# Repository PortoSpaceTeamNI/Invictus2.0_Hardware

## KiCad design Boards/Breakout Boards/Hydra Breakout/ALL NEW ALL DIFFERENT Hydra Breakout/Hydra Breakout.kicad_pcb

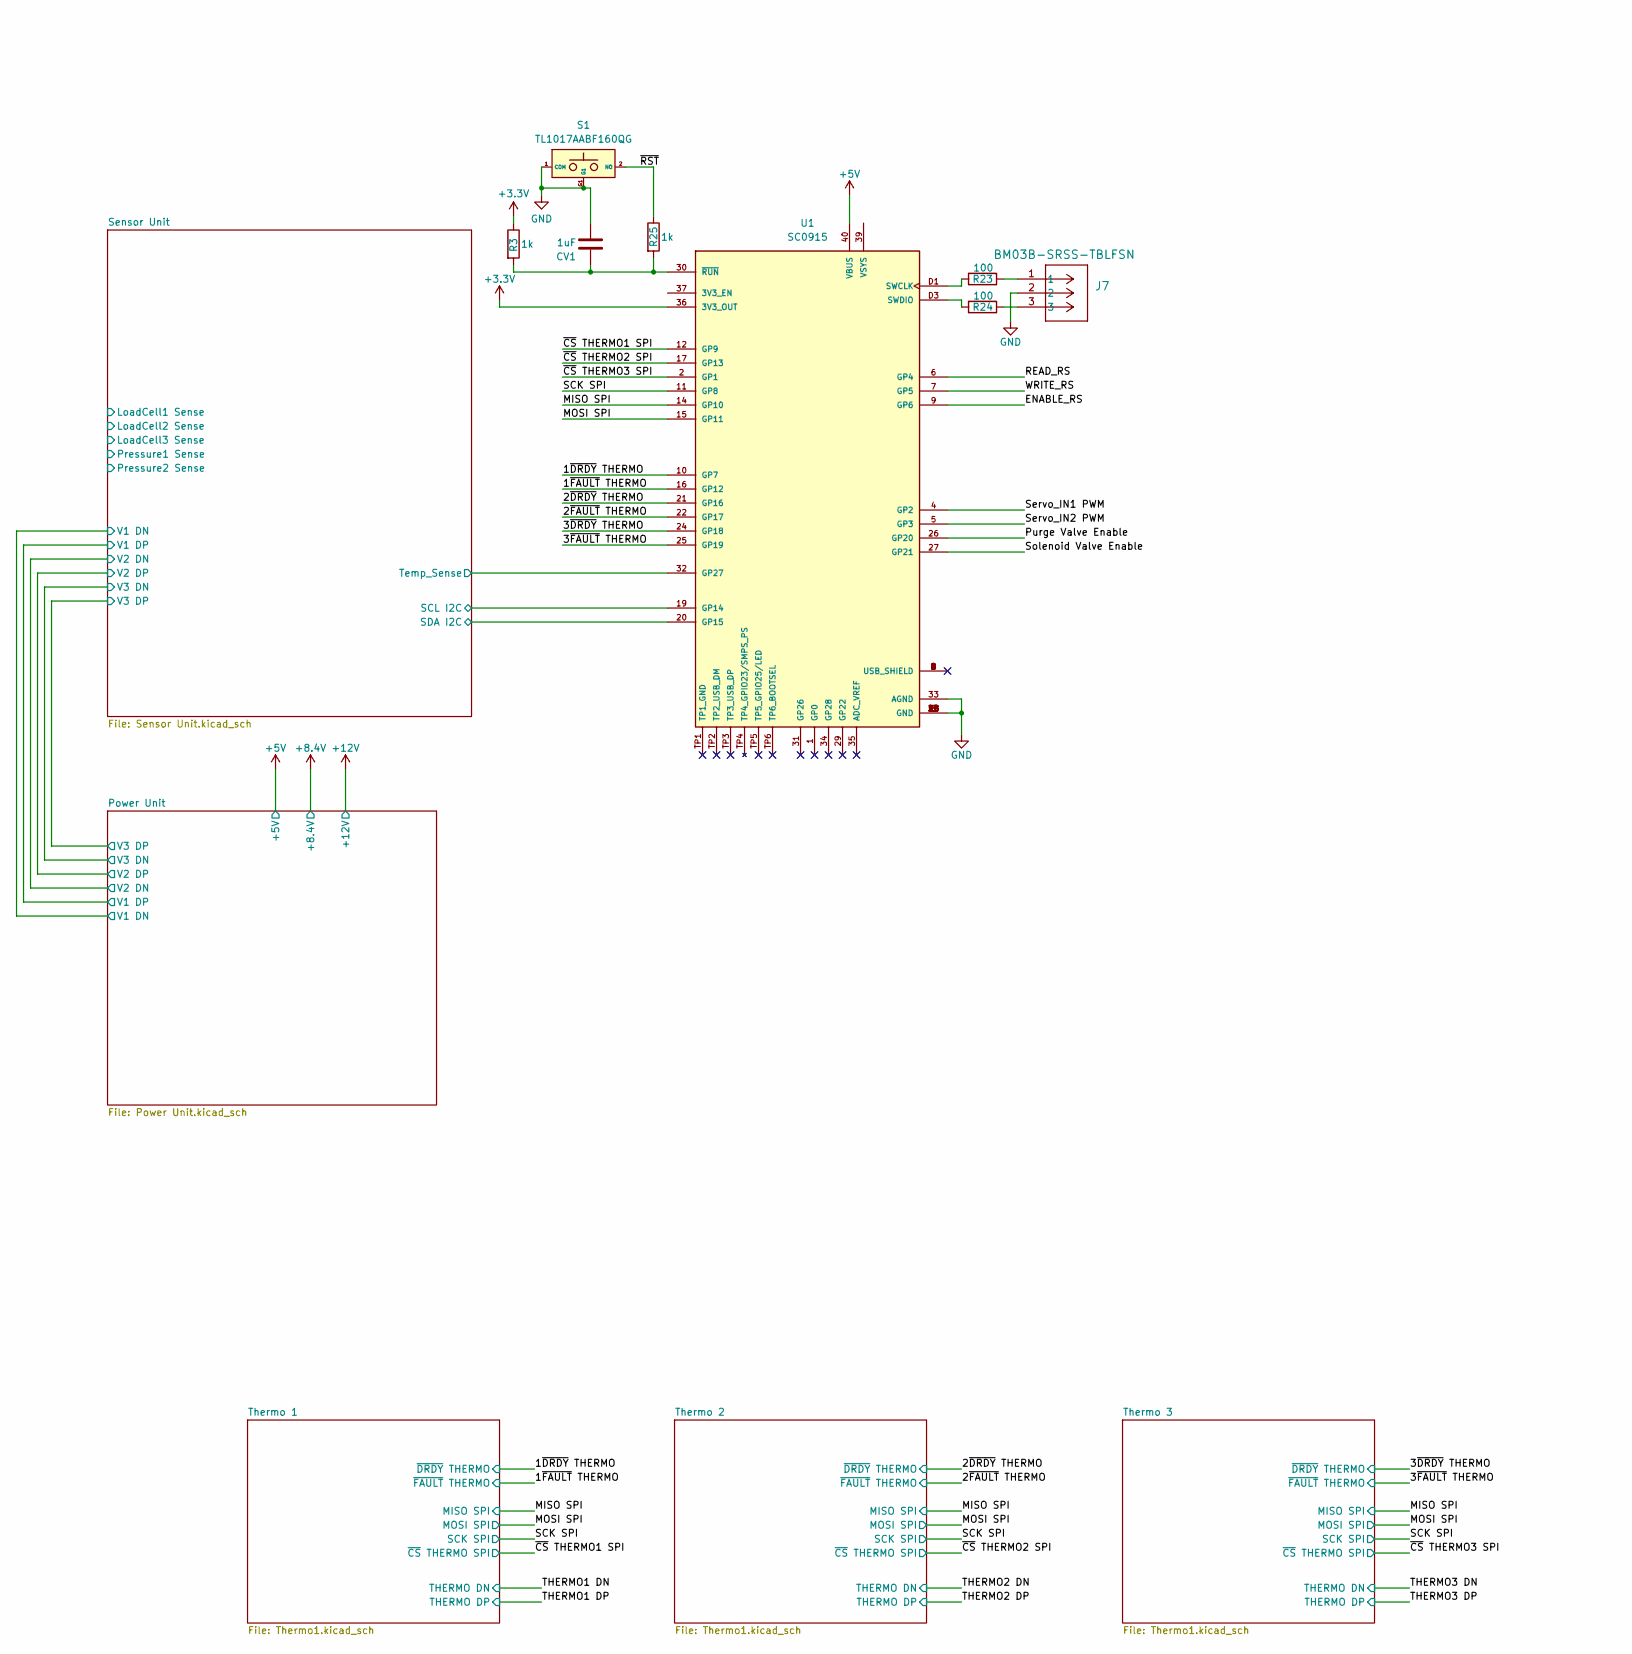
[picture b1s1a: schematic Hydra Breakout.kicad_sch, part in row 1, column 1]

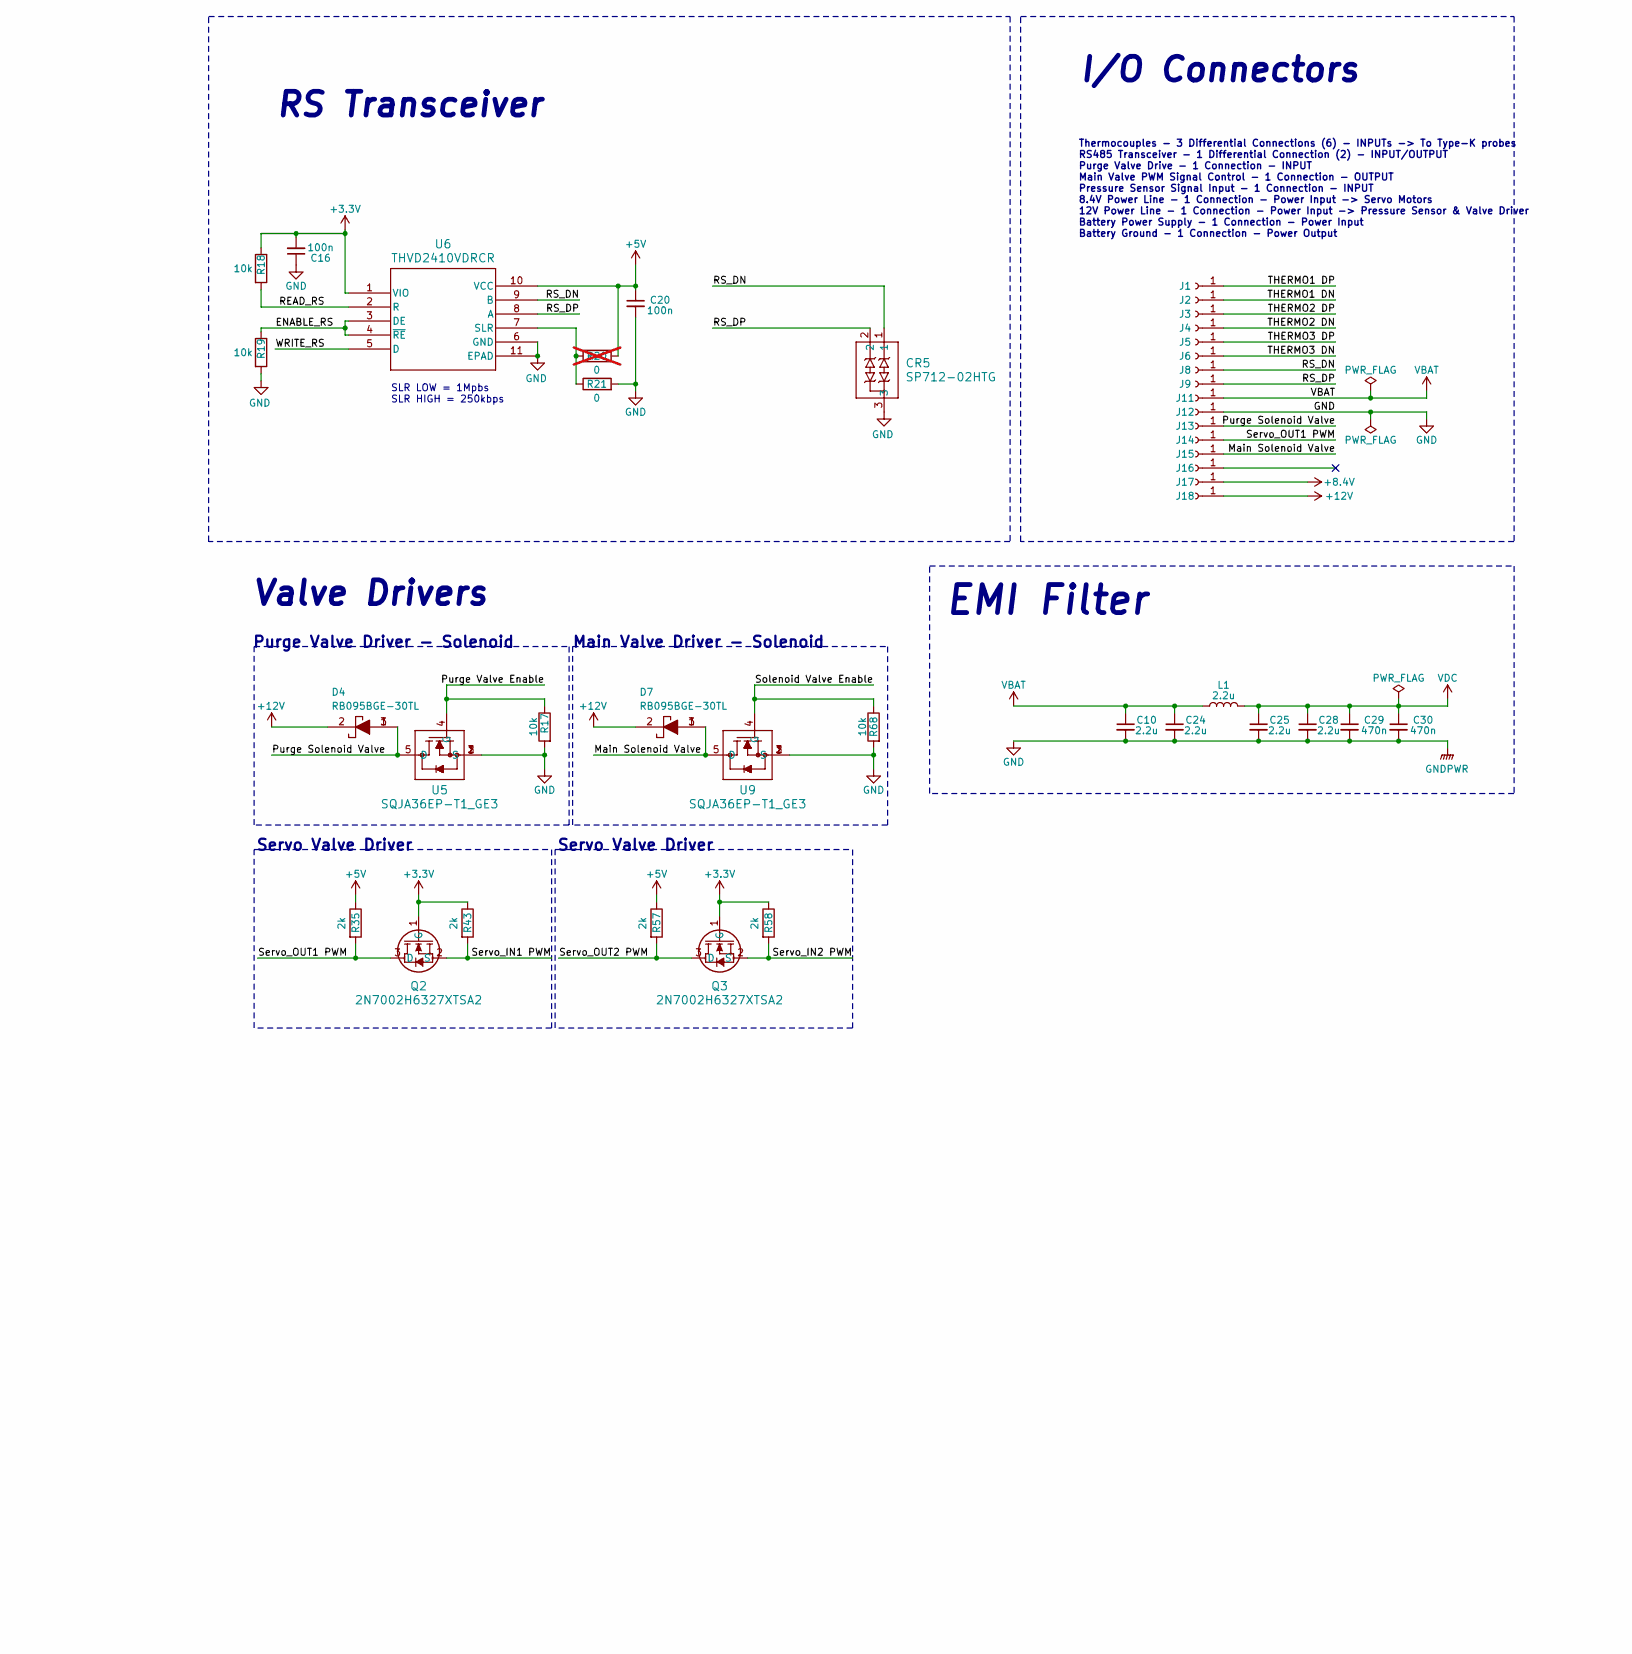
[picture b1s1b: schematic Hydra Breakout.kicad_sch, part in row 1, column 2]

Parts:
C10, C24, C25, C28: 2.2u; Capacitor_1206
C16, C20: 100n; Capacitor_0603
C29, C30: 470n; Capacitor_1206
CR5: SP712-02HTG; SOT23-3_LTF
CV1: 1uF; Capacitor_0603
D4, D7: RB095BGE-30TL; RD3P175SNFRATL; Mouser Part Number 755-RB095BGE-30TL
J1, J2, J3, J4, J5, J6, J8, J9, J11, J12, J13, J14, J15, J16, J17, J18: Conn_01x01_Socket; Pico_01pin
J7: BM03B-SRSS-TBLFSN; CONN_BM03B-SRSS-TBLFSN_JST
L1: 2.2u; IND_SPM10065VT-2R2M-D
Q2, Q3: 2N7002H6327XTSA2; PG-SOT23-3-5_INF_MIN
R3, R25: 1k; Capacitor_0603
R17, R18, R19, R68: 10k; Capacitor_0603
R20: 0; RES_0603; not fitted
R21: 0; RES_0603
R23, R24: 100; Capacitor_0603
R35, R43, R57, R58: 2k; Capacitor_0603
S1: TL1017AABF160QG; Mouser Part Number 612-TL1017AABF160QG
U1: SC0915; MODULE_SC0915; PARTREV 1.9
U5, U9: SQJA36EP-T1_GE3; PowerPAK_SO-8L_3_VIS
U6: THVD2410VDRCR; VSON10_DRC_TEX

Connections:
+3.3V: C16.2, Q2.1 (G), Q3.1 (G), R3.1, R18.1, R43.1, R58.1, U1.36 (3V3_OUT), U6.1 (VIO); also elsewhere on the board
+5V: C20.1, R20.2, R35.1, R57.1, U1.40 (VBUS), U6.10 (VCC); also elsewhere on the board
+8.4V: J17.1; also elsewhere on the board
+12V: D4.2, D7.2, J18.1; also elsewhere on the board
/1~DRDY THERMO: U1.10 (GP7); also elsewhere on the board
/1~FAULT THERMO: U1.16 (GP12); also elsewhere on the board
/2~DRDY THERMO: U1.21 (GP16); also elsewhere on the board
/2~FAULT THERMO: U1.22 (GP17); also elsewhere on the board
/3~DRDY THERMO: U1.24 (GP18); also elsewhere on the board
/3~FAULT THERMO: U1.25 (GP19); also elsewhere on the board
/ENABLE_RS: R19.1, U1.9 (GP6), U6.3 (DE), U6.4 (~RE)
/MISO SPI: U1.14 (GP10); also elsewhere on the board
/MOSI SPI: U1.15 (GP11); also elsewhere on the board
/Main Solenoid Valve: D7.1, D7.3, J15.1, U9.5 (D)
/Purge Solenoid Valve: D4.1, D4.3, J13.1, U5.5 (D)
/Purge Valve Enable: R17.1, U1.26 (GP20), U5.4 (G)
/READ_RS: R18.2, U1.6 (GP4), U6.2 (R); also elsewhere on the board
/RS_DN: CR5.1, J8.1, U6.9 (B); also elsewhere on the board
/RS_DP: CR5.2, J9.1, U6.8 (A); also elsewhere on the board
/SCK SPI: U1.11 (GP8); also elsewhere on the board
/Sensor Unit/SCL I2C: U1.19 (GP14); also elsewhere on the board
/Sensor Unit/SDA I2C: U1.20 (GP15); also elsewhere on the board
/Sensor Unit/Temp_Sense: U1.32 (GP27); also elsewhere on the board
/Servo_IN1 PWM: Q2.2 (S), R43.2, U1.4 (GP2)
/Servo_IN2 PWM: Q3.2 (S), R58.2, U1.5 (GP3)
/Servo_OUT1 PWM: J14.1, Q2.3 (D), R35.2
/Servo_OUT2 PWM: Q3.3 (D), R57.2
/Solenoid Valve Enable: R68.1, U1.27 (GP21), U9.4 (G)
/THERMO1 DN: J2.1; also elsewhere on the board
/THERMO1 DP: J1.1; also elsewhere on the board
/THERMO2 DN: J4.1; also elsewhere on the board
/THERMO2 DP: J3.1; also elsewhere on the board
/THERMO3 DN: J6.1; also elsewhere on the board
/THERMO3 DP: J5.1; also elsewhere on the board
/WRITE_RS: U1.7 (GP5), U6.5 (D)
/~CS THERMO1 SPI: U1.12 (GP9); also elsewhere on the board
/~CS THERMO2 SPI: U1.17 (GP13); also elsewhere on the board
/~CS THERMO3 SPI: U1.2 (GP1); also elsewhere on the board
/~RST: R25.1, S1.2 (NO)
GND: C10.2, C16.1, C20.2, C24.2, C25.2, C28.2, C29.2, C30.2, CR5.3, CV1.2, J7.2, J12.1, R17.2, R19.2, R21.2, R68.2, S1.1 (COM), S1.G1, U1.3 (GND), U1.8 (GND), U1.13 (GND), U1.18 (GND), U1.23 (GND), U1.28 (GND), U1.33 (AGND), U1.38 (GND), U1.D2 (GND), U5.1 (S), U5.2 (S), U5.3 (S), U6.6 (GND), U6.11 (EPAD), U9.1 (S), U9.2 (S), U9.3 (S); also elsewhere on the board
unnamed: J7.1, R23.1
unnamed: J7.3, R24.1
unnamed: R23.2, U1.D1 (SWCLK)
unnamed: R24.2, U1.D3 (SWDIO)
unnamed: CV1.1, R3.2, R25.2, U1.30 (~RUN)
unnamed: R20.1, R21.1, U6.7 (SLR)
VBAT: C10.1, C24.1, J11.1, L1.1
VDC: C25.1, C28.1, C29.1, C30.1, L1.2; also elsewhere on the board

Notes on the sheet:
EMI Filter
Thermocouples - 3 Differential Connections (6) - INPUTs -> To Type-K probes RS485 Transceiver - 1 Differential Connection (2) - INPUT/OUTPUT Purge Valve Drive - 1 Connection - INPUT Main Valve PWM Signal Control - 1 Connection - OUTPUT Pressure Sensor Signal Input - 1 Connection - INPUT 8.4V Power 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
Purge Valve Driver - Solenoid
Servo Valve Driver
SLR LOW = 1Mpbs SLR HIGH = 250kbps
I/O Connectors
Main Valve Driver - Solenoid
RS Transceiver
Valve Drivers

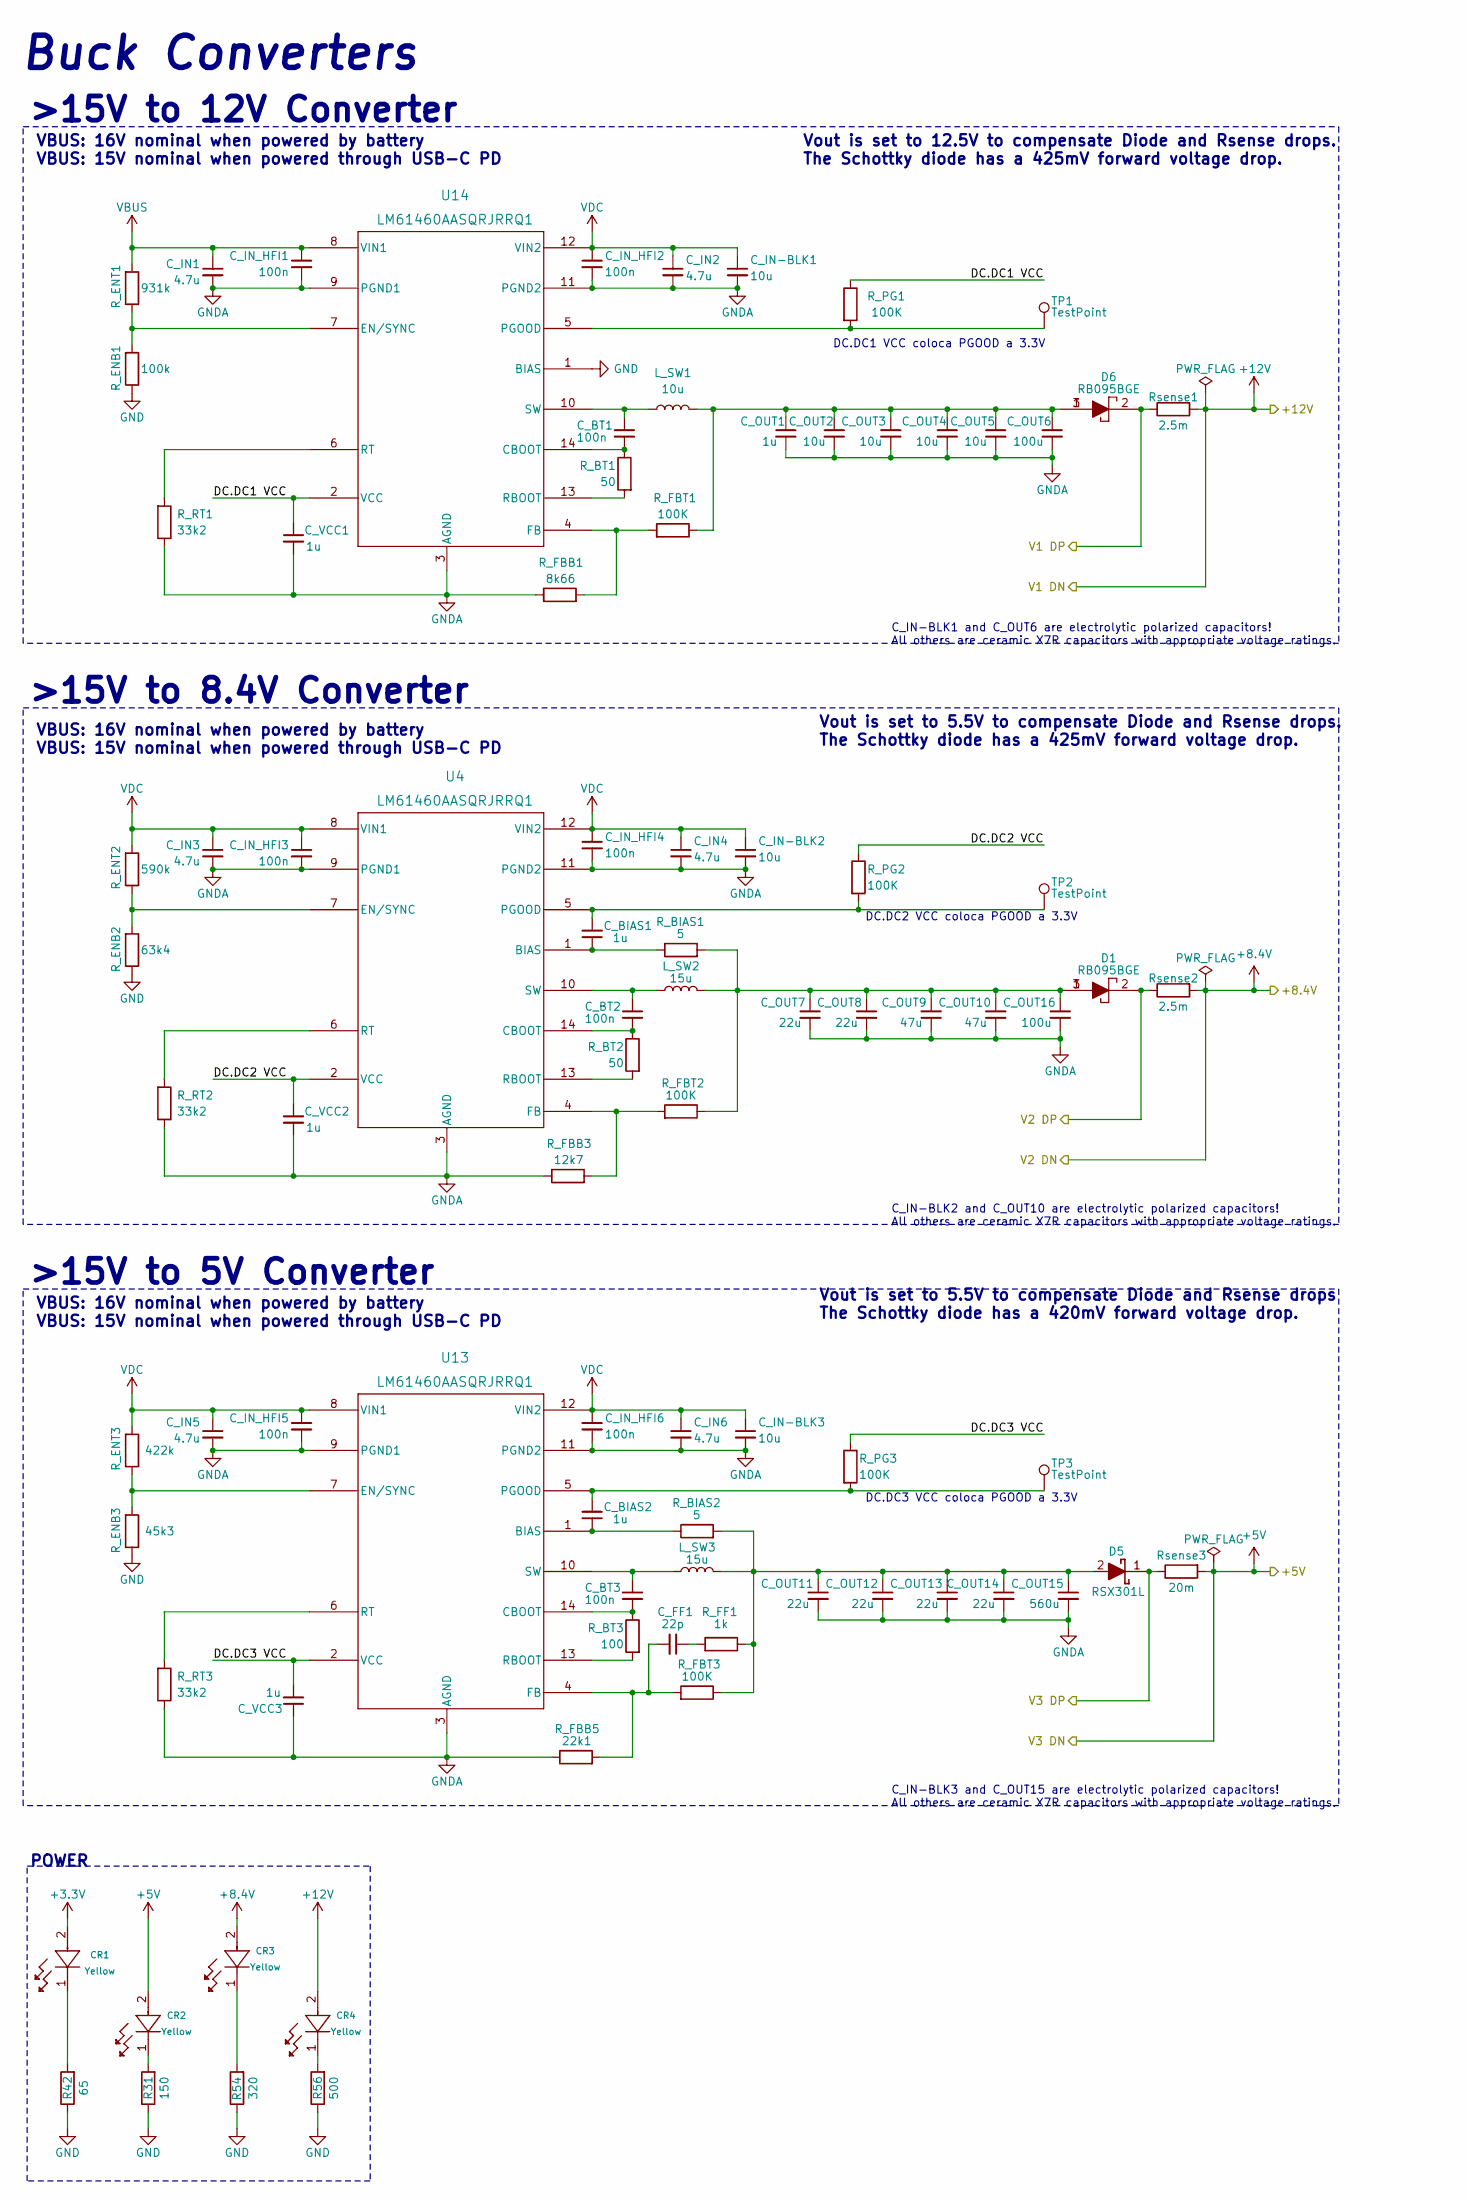
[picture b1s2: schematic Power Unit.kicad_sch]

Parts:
CR1, CR2, CR3, CR4: VLMY1300-GS08; LEDC1608X100N
C_BIAS1, C_BIAS2: 1u; Capacitor_0603
C_BT1, C_BT2, C_BT3: 100n; Capacitor_0603
C_FF1: 22p; Capacitor_0603
C_IN1, C_IN2, C_IN3, C_IN4, C_IN5, C_IN6: 4.7u; Capacitor_1206
C_IN-BLK1, C_IN-BLK2, C_IN-BLK3: 10u; Capacitor_4mm
C_IN_HFI1, C_IN_HFI2, C_IN_HFI3, C_IN_HFI4, C_IN_HFI5, C_IN_HFI6: 100n; Capacitor_0603
C_OUT1: 1u; Capacitor_0603
C_OUT2, C_OUT3, C_OUT4, C_OUT5: 10u; Capacitor_0805
C_OUT6: 100u; Capacitor_6mm
C_OUT7, C_OUT8, C_OUT11, C_OUT12, C_OUT13, C_OUT14: 22u; Capacitor_0805
C_OUT9, C_OUT10: 47u; Capacitor_0805
C_OUT15: 560u; Capacitor_8mm
C_OUT16: 100u; Capacitor_8mm
C_VCC1, C_VCC2, C_VCC3: 1u; Capacitor_0603
D1, D6: RB095BGE; RD3P175SNFRATL; Mouser Part Number 755-RB095BGE-30TL
D5: RSX301L; DIOM5026X220N; Mouser Part Number 755-RSX301L-30DDTE25
L_SW1: 10u; Inductor_11.5x10
L_SW2, L_SW3: 15u; Inductor_10.1x10
R31: 150; Capacitor_0603
R42: 65; Capacitor_0603
R54: 320; Capacitor_0603
R56: 500; Capacitor_0603
R_BIAS1, R_BIAS2: 5; Capacitor_0603
R_BT1, R_BT2: 50; Capacitor_0603
R_BT3: 100; Capacitor_0603
R_ENB1: 100k; RES_0603
R_ENB2: 63k4; Capacitor_0603
R_ENB3: 45k3; Capacitor_0603
R_ENT1: 931k; RES_0603
R_ENT2: 590k; Capacitor_0603
R_ENT3: 422k; Capacitor_0603
R_FBB1: 8k66; RES_0603
R_FBB3: 12k7; RES_0603
R_FBB5: 22k1; RES_0603
R_FBT1, R_FBT2, R_FBT3: 100K; RES_0603
R_FF1: 1k; Capacitor_0603
R_PG1, R_PG2, R_PG3: 100K; RES_0603
R_RT1, R_RT2, R_RT3: 33k2; RES_0603
Rsense1, Rsense2: 2.5m; RES_0805
Rsense3: 20m; RES_WSLP2512
TP1, TP2, TP3: TestPoint; TestPoint_Pad_2.0x2.0mm
U4, U13, U14: LM61460AASQRJRRQ1; VQFN-HR14_RJR_TEX

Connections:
+3.3V: CR1.2; also elsewhere on the board
+5V: CR2.2, Rsense3.2; also elsewhere on the board
+8.4V: CR3.2, Rsense2.2; also elsewhere on the board
+12V: CR4.2, Rsense1.2; also elsewhere on the board
/Power Unit/DC.DC1 VCC: C_VCC1.1, R_PG1.1, U14.2 (VCC)
/Power Unit/DC.DC2 VCC: C_VCC2.1, R_PG2.1, U4.2 (VCC)
/Power Unit/DC.DC3 VCC: C_VCC3.2, R_PG3.1, U13.2 (VCC)
/Power Unit/V1 DP: D6.2, Rsense1.1; also elsewhere on the board
/Power Unit/V2 DP: D1.2, Rsense2.1; also elsewhere on the board
/Power Unit/V3 DP: D5.1 (K), Rsense3.1; also elsewhere on the board
GND: R31.1, R42.1, R54.1, R56.1, R_ENB1.1, R_ENB2.1, R_ENB3.1, U14.1 (BIAS); also elsewhere on the board
GNDA: C_IN1.2, C_IN2.2, C_IN3.2, C_IN4.2, C_IN5.2, C_IN6.2, C_IN-BLK1.2, C_IN-BLK2.2, C_IN-BLK3.2, C_IN_HFI1.2, C_IN_HFI2.2, C_IN_HFI3.2, C_IN_HFI4.2, C_IN_HFI5.2, C_IN_HFI6.2, C_OUT1.2, C_OUT2.2, C_OUT3.2, C_OUT4.2, C_OUT5.2, C_OUT6.2, C_OUT7.2, C_OUT8.2, C_OUT9.2, C_OUT10.2, C_OUT11.2, C_OUT12.2, C_OUT13.2, C_OUT14.2, C_OUT15.2, C_OUT16.2, C_VCC1.2, C_VCC2.2, C_VCC3.1, R_FBB1.1, R_FBB3.1, R_FBB5.1, R_RT1.1, R_RT2.1, R_RT3.1, U4.3 (AGND), U4.9 (PGND1), U4.11 (PGND2), U13.3 (AGND), U13.9 (PGND1), U13.11 (PGND2), U14.3 (AGND), U14.9 (PGND1), U14.11 (PGND2); also elsewhere on the board
unnamed: CR1.1, R42.2
unnamed: CR2.1, R31.2
unnamed: CR3.1, R54.2
unnamed: CR4.1, R56.2
unnamed: C_FF1.1, R_FF1.2
unnamed: C_OUT1.1, C_OUT2.1, C_OUT3.1, C_OUT4.1, C_OUT5.1, C_OUT6.1, D6.1, D6.3, L_SW1.2, R_FBT1.1
unnamed: C_OUT7.1, C_OUT8.1, C_OUT9.1, C_OUT10.1, C_OUT16.1, D1.1, D1.3, L_SW2.2, R_BIAS1.2, R_FBT2.1
unnamed: C_OUT11.1, C_OUT12.1, C_OUT13.1, C_OUT14.1, C_OUT15.1, D5.2 (A), L_SW3.2, R_BIAS2.2, R_FBT3.1, R_FF1.1
unnamed: C_BIAS1.1, R_BIAS1.1, U4.1 (BIAS)
unnamed: C_BT2.2, R_BT2.1, U4.14 (CBOOT)
unnamed: R_ENB2.2, R_ENT2.1, U4.7 (EN/SYNC)
unnamed: R_FBB3.2, R_FBT2.2, U4.4 (FB)
unnamed: C_BIAS1.2, R_PG2.2, TP2.1, U4.5 (PGOOD)
unnamed: R_BT2.2, U4.13 (RBOOT)
unnamed: R_RT2.2, U4.6 (RT)
unnamed: C_BT2.1, L_SW2.1, U4.10 (SW)
unnamed: C_BIAS2.1, R_BIAS2.1, U13.1 (BIAS)
unnamed: C_BT3.2, R_BT3.1, U13.14 (CBOOT)
unnamed: R_ENB3.2, R_ENT3.1, U13.7 (EN/SYNC)
unnamed: C_FF1.2, R_FBB5.2, R_FBT3.2, U13.4 (FB)
unnamed: C_BIAS2.2, R_PG3.2, TP3.1, U13.5 (PGOOD)
unnamed: R_BT3.2, U13.13 (RBOOT)
unnamed: R_RT3.2, U13.6 (RT)
unnamed: C_BT3.1, L_SW3.1, U13.10 (SW)
unnamed: C_BT1.2, R_BT1.1, U14.14 (CBOOT)
unnamed: R_ENB1.2, R_ENT1.1, U14.7 (EN/SYNC)
unnamed: R_FBB1.2, R_FBT1.2, U14.4 (FB)
unnamed: R_PG1.2, TP1.1, U14.5 (PGOOD)
unnamed: R_BT1.2, U14.13 (RBOOT)
unnamed: R_RT1.2, U14.6 (RT)
unnamed: C_BT1.1, L_SW1.1, U14.10 (SW)
VBUS: C_IN1.1, C_IN_HFI1.1, R_ENT1.2, U14.8 (VIN1)
VDC: C_IN2.1, C_IN3.1, C_IN4.1, C_IN5.1, C_IN6.1, C_IN-BLK1.1, C_IN-BLK2.1, C_IN-BLK3.1, C_IN_HFI2.1, C_IN_HFI3.1, C_IN_HFI4.1, C_IN_HFI5.1, C_IN_HFI6.1, R_ENT2.2, R_ENT3.2, U4.8 (VIN1), U4.12 (VIN2), U13.8 (VIN1), U13.12 (VIN2), U14.12 (VIN2); also elsewhere on the board

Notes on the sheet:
VBUS: 16V nominal when powered by battery VBUS: 15V nominal when powered through USB-C PD
Buck Converters
Vout is set to 12.5V to compensate Diode and Rsense drops. The Schottky diode has a 425mV forward voltage drop.
C_IN-BLK2 and C_OUT10 are electrolytic polarized capacitors! All others are ceramic X7R capacitors with appropriate voltage ratings.
DC.DC3 VCC coloca PGOOD a 3.3V
>15V to 8.4V Converter
>15V to 12V Converter
DC.DC2 VCC coloca PGOOD a 3.3V
>15V to 5V Converter
C_IN-BLK1 and C_OUT6 are electrolytic polarized capacitors! All others are ceramic X7R capacitors with appropriate voltage ratings.
C_IN-BLK3 and C_OUT15 are electrolytic polarized capacitors! All others are ceramic X7R capacitors with appropriate voltage ratings.
Vout is set to 5.5V to compensate Diode and Rsense drops. The Schottky diode has a 425mV forward voltage drop.
DC.DC1 VCC coloca PGOOD a 3.3V
POWER
Vout is set to 5.5V to compensate Diode and Rsense drops The Schottky diode has a 420mV forward voltage drop.

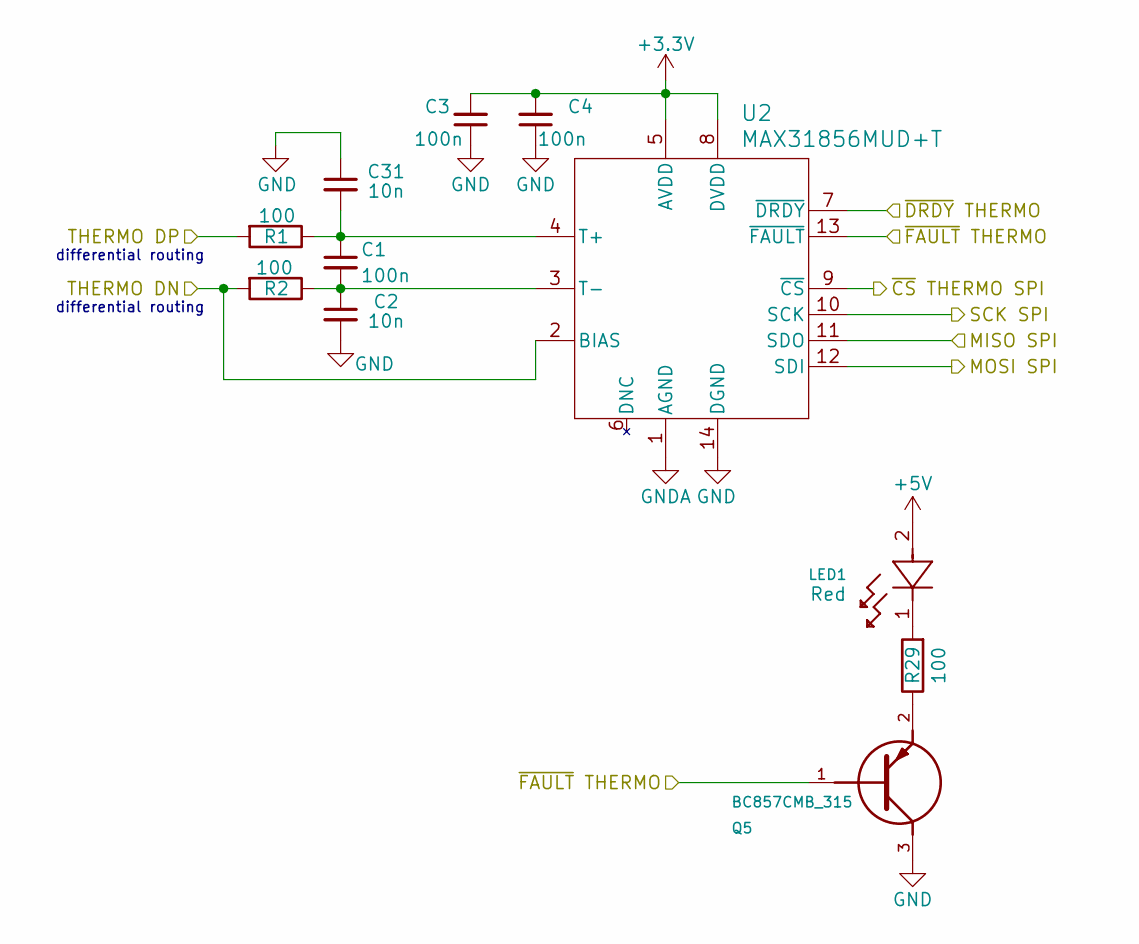
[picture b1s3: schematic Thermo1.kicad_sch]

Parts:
C1, C3, C4: 100n; Capacitor_0603
C2, C31: 10n; Capacitor_0603
LED1: VLMS1500-GS08; LED_00-GS08_VIS_RED
Q5: BC857CMB_315; TRANS_PMZB550UNEYL
R1, R2, R29: 100; Capacitor_0603
U2: MAX31856MUD+T; 21-0066J_14_MXM

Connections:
+3.3V: C3.2, C4.2, U2.5 (AVDD), U2.8 (DVDD); also elsewhere on the board
+5V: LED1.2; also elsewhere on the board
/1~DRDY THERMO: U2.7 (~DRDY); also elsewhere on the board
/1~FAULT THERMO: Q5.1, U2.13 (~FAULT); also elsewhere on the board
/MISO SPI: U2.11 (SDO); also elsewhere on the board
/MOSI SPI: U2.12 (SDI); also elsewhere on the board
/SCK SPI: U2.10 (SCK); also elsewhere on the board
/THERMO1 DN: R2.2, U2.2 (BIAS); also elsewhere on the board
/THERMO1 DP: R1.2; also elsewhere on the board
/~CS THERMO1 SPI: U2.9 (~CS); also elsewhere on the board
GND: C2.2, C3.1, C4.1, C31.1, Q5.3, U2.14 (DGND); also elsewhere on the board
GNDA: U2.1 (AGND); also elsewhere on the board
unnamed: LED1.1, R29.2
unnamed: Q5.2, R29.1
unnamed: C1.1, C31.2, R1.1, U2.4 (T+)
unnamed: C1.2, C2.1, R2.1, U2.3 (T-)

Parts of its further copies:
C5, C7, C8, C9, C12, C13: 100n; Capacitor_0603
C6, C11, C32, C34: 10n; Capacitor_0603
LED2, LED3: VLMS1500-GS08; LED_00-GS08_VIS_RED
Q6, Q7: BC857CMB_315; TRANS_PMZB550UNEYL
R4, R5, R10, R11, R30, R32: 100; Capacitor_0603
U3, U7: MAX31856MUD+T; 21-0066J_14_MXM

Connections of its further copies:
+3.3V: C7.2, C8.2, C12.2, C13.2, U3.5 (AVDD), U3.8 (DVDD), U7.5 (AVDD), U7.8 (DVDD); also elsewhere on the board
+5V: LED2.2, LED3.2; also elsewhere on the board
/2~DRDY THERMO: U3.7 (~DRDY); also elsewhere on the board
/2~FAULT THERMO: Q6.1, U3.13 (~FAULT); also elsewhere on the board
/3~DRDY THERMO: U7.7 (~DRDY); also elsewhere on the board
/3~FAULT THERMO: Q7.1, U7.13 (~FAULT); also elsewhere on the board
/MISO SPI: U3.11 (SDO), U7.11 (SDO); also elsewhere on the board
/MOSI SPI: U3.12 (SDI), U7.12 (SDI); also elsewhere on the board
/SCK SPI: U3.10 (SCK), U7.10 (SCK); also elsewhere on the board
/THERMO2 DN: R5.2, U3.2 (BIAS); also elsewhere on the board
/THERMO2 DP: R4.2; also elsewhere on the board
/THERMO3 DN: R11.2, U7.2 (BIAS); also elsewhere on the board
/THERMO3 DP: R10.2; also elsewhere on the board
/~CS THERMO2 SPI: U3.9 (~CS); also elsewhere on the board
/~CS THERMO3 SPI: U7.9 (~CS); also elsewhere on the board
GND: C6.2, C7.1, C8.1, C11.2, C12.1, C13.1, C32.1, C34.1, Q6.3, Q7.3, U3.14 (DGND), U7.14 (DGND); also elsewhere on the board
GNDA: U3.1 (AGND), U7.1 (AGND); also elsewhere on the board
unnamed: LED2.1, R30.2
unnamed: LED3.1, R32.2
unnamed: Q6.2, R30.1
unnamed: Q7.2, R32.1
unnamed: C5.1, C32.2, R4.1, U3.4 (T+)
unnamed: C5.2, C6.1, R5.1, U3.3 (T-)
unnamed: C9.1, C34.2, R10.1, U7.4 (T+)
unnamed: C9.2, C11.1, R11.1, U7.3 (T-)

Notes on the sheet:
differential routing

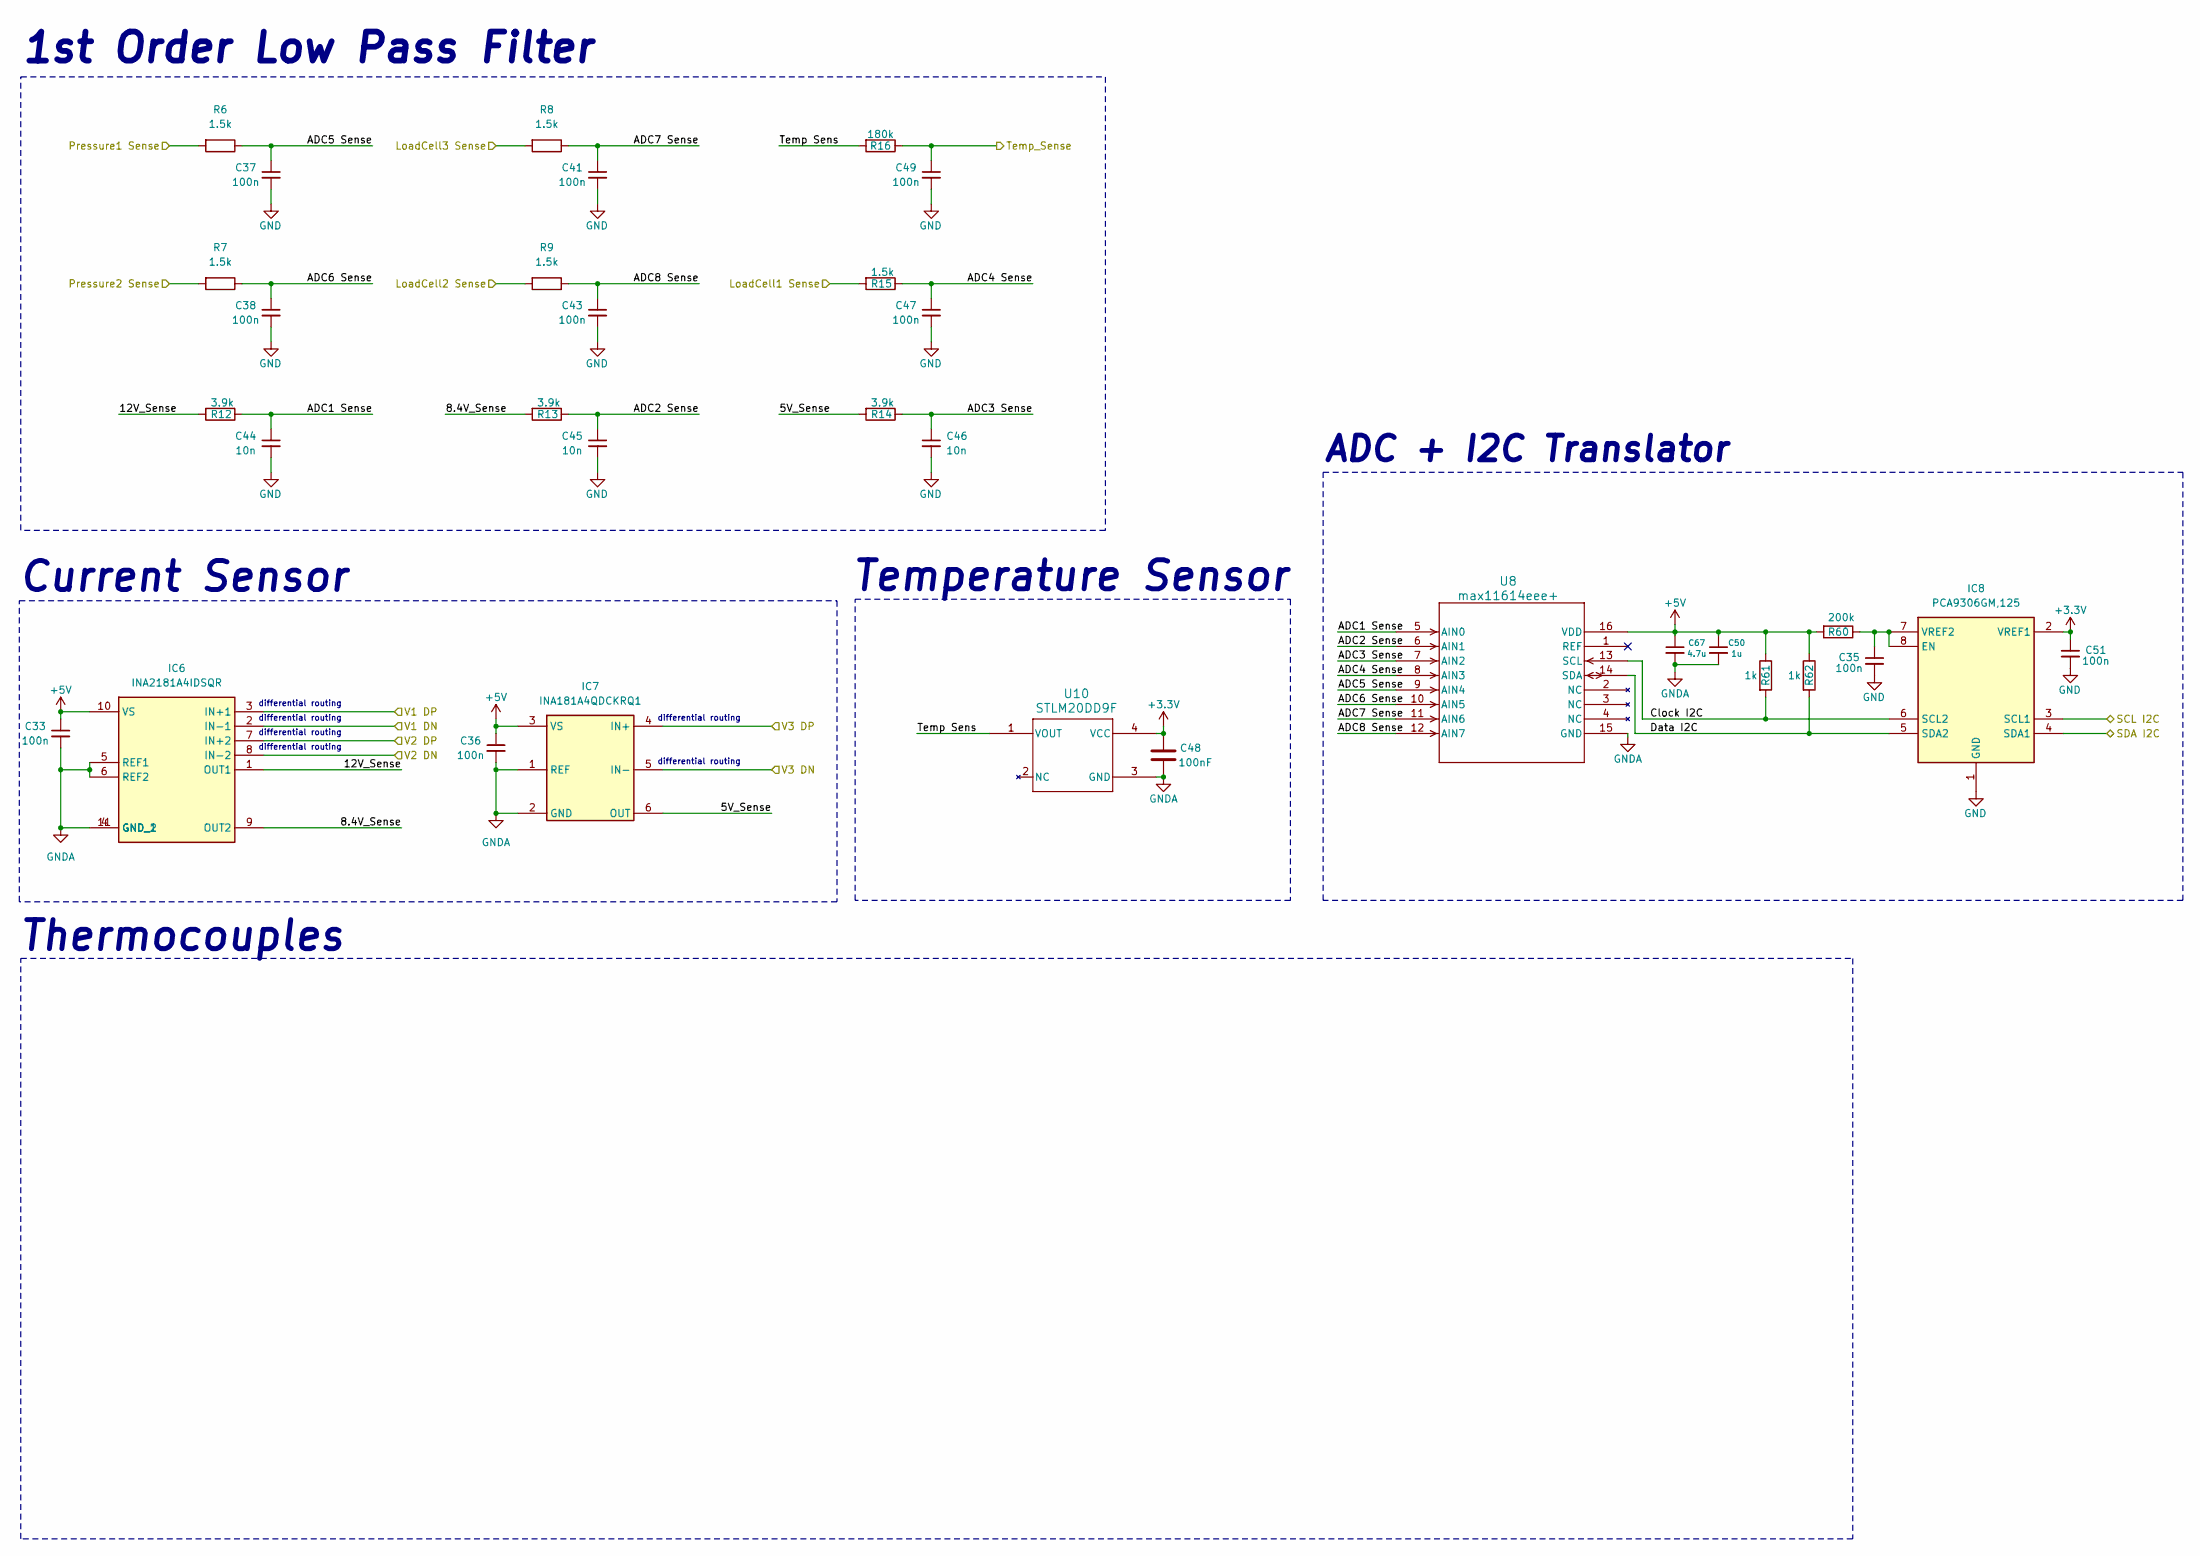
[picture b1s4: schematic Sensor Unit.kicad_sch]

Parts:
C33, C35, C36, C37, C38, C41, C43, C47, C49, C51: 100n; Capacitor_0603
C44, C45, C46: 10n; Capacitor_0603
C48: 100nF; Capacitor_0603
C50: 1u; Capacitor_0603
C67: 4.7u; Capacitor_1206
IC6: INA2181A4IDSQR; SON40P200X200X80-11N; Mouser Part Number 595-INA2181A4IDSQR
IC7: INA181A4QDCKRQ1; SOT65P210X110-6N; Mouser Part Number 595-INA181A4QDCKRQ1
IC8: PCA9306GM,125; PCA9570GMH; Mouser Part Number 771-PCA9306GM125
R6, R7, R8, R9, R15: 1.5k; Capacitor_0603
R12, R13, R14: 3.9k; Capacitor_0603
R16: 180k; Capacitor_0603
R60: 200k; Capacitor_0603
R61, R62: 1k; Capacitor_0603
U8: max11614eee+; SOP64P602X175-16N
U10: STLM20DD9F; UDFN-4L_STM

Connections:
+3.3V: C48.1, C51.1, IC8.2 (VREF1), U10.4 (VCC); also elsewhere on the board
+5V: C33.1, C36.1, C50.1, C67.1, IC6.10 (VS), IC7.3 (VS), IC7.5 (IN-), R60.2, R61.1, R62.1, U8.16 (VDD); also elsewhere on the board
+8.4V: IC6.8 (IN-2); also elsewhere on the board
+12V: IC6.2 (IN-1); also elsewhere on the board
/Power Unit/V1 DP: IC6.3 (IN+1); also elsewhere on the board
/Power Unit/V2 DP: IC6.7 (IN+2); also elsewhere on the board
/Power Unit/V3 DP: IC7.4 (IN+); also elsewhere on the board
/Sensor Unit/5V_Sense: IC7.6 (OUT), R14.2
/Sensor Unit/8.4V_Sense: IC6.9 (OUT2), R13.2
/Sensor Unit/12V_Sense: IC6.1 (OUT1), R12.2
/Sensor Unit/ADC1 Sense: C44.1, R12.1, U8.5 (AIN0)
/Sensor Unit/ADC2 Sense: C45.1, R13.1, U8.6 (AIN1)
/Sensor Unit/ADC3 Sense: C46.1, R14.1, U8.7 (AIN2)
/Sensor Unit/ADC4 Sense: C47.1, R15.1, U8.8 (AIN3)
/Sensor Unit/ADC5 Sense: C37.1, R6.1, U8.9 (AIN4)
/Sensor Unit/ADC6 Sense: C38.1, R7.1, U8.10 (AIN5)
/Sensor Unit/ADC7 Sense: C41.1, R8.1, U8.11 (AIN6)
/Sensor Unit/ADC8 Sense: C43.1, R9.1, U8.12 (AIN7)
/Sensor Unit/Clock I2C: IC8.6 (SCL2), R61.2, U8.13 (SCL)
/Sensor Unit/Data I2C: IC8.5 (SDA2), R62.2, U8.14 (SDA)
/Sensor Unit/LoadCell1 Sense: R15.2
/Sensor Unit/LoadCell2 Sense: R9.2
/Sensor Unit/LoadCell3 Sense: R8.2
/Sensor Unit/Pressure1 Sense: R6.2
/Sensor Unit/Pressure2 Sense: R7.2
/Sensor Unit/SCL I2C: IC8.3 (SCL1); also elsewhere on the board
/Sensor Unit/SDA I2C: IC8.4 (SDA1); also elsewhere on the board
/Sensor Unit/Temp Sens: R16.2, U10.1 (VOUT)
/Sensor Unit/Temp_Sense: C49.1, R16.1; also elsewhere on the board
GND: C35.2, C37.2, C38.2, C41.2, C43.2, C44.2, C45.2, C46.2, C47.2, C49.2, C51.2, IC8.1 (GND); also elsewhere on the board
GNDA: C33.2, C36.2, C48.2, C50.2, C67.2, IC6.4 (GND_1), IC6.5 (REF1), IC6.6 (REF2), IC6.11 (GND_2), IC7.1 (REF), IC7.2 (GND), U8.15 (GND), U10.3 (GND); also elsewhere on the board
unnamed: C35.1, IC8.7 (VREF2), IC8.8 (EN), R60.1

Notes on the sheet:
differential routing
Current Sensor
Temperature Sensor
Thermocouples
1st Order Low Pass Filter
ADC + I2C Translator

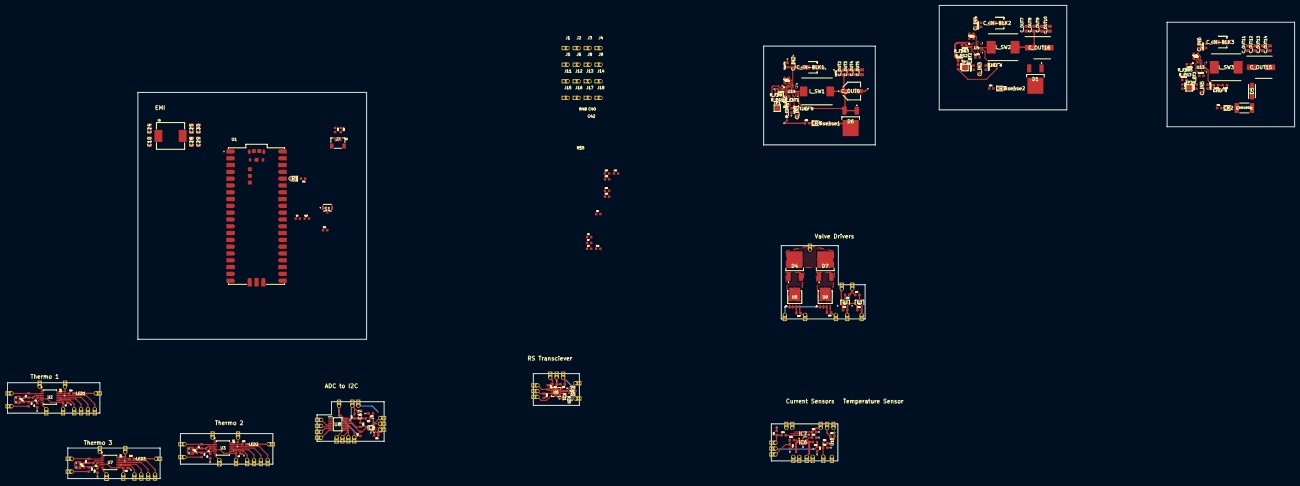
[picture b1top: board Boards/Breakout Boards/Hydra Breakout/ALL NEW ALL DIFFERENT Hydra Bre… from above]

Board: 2 copper layers, 480.7 x 176.7 mm, 208 parts (0 on the bottom side), 114 nets.

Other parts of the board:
C40, C42: 100n; Capacitor_0402
R48: 10k; RES_0402
R55: 120; RES_0603

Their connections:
+3.3V: C42.2, R48.1; also elsewhere on the board
+5V: C40.1; also elsewhere on the board
/READ_RS: R48.2; also elsewhere on the board
/RS_DN: R55.1; also elsewhere on the board
/RS_DP: R55.2; also elsewhere on the board
GND: C40.2, C42.1; also elsewhere on the board
